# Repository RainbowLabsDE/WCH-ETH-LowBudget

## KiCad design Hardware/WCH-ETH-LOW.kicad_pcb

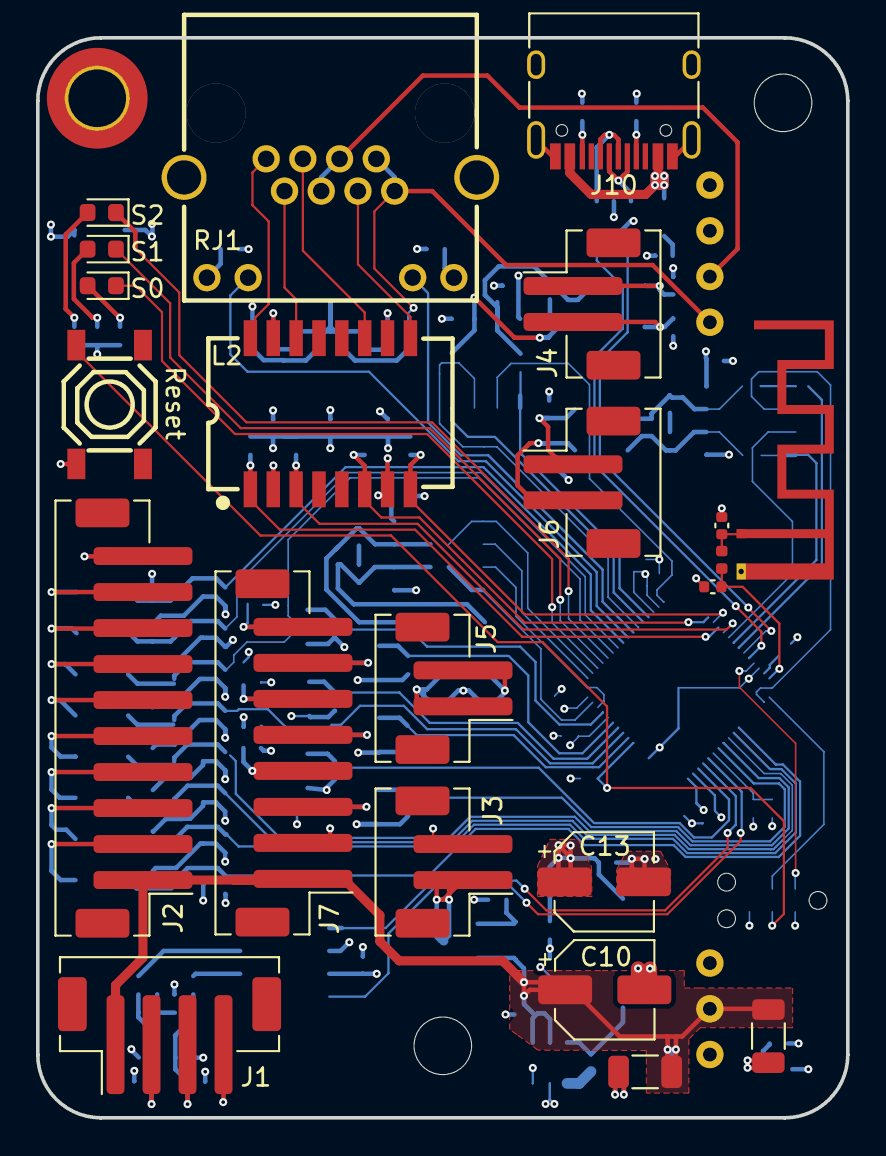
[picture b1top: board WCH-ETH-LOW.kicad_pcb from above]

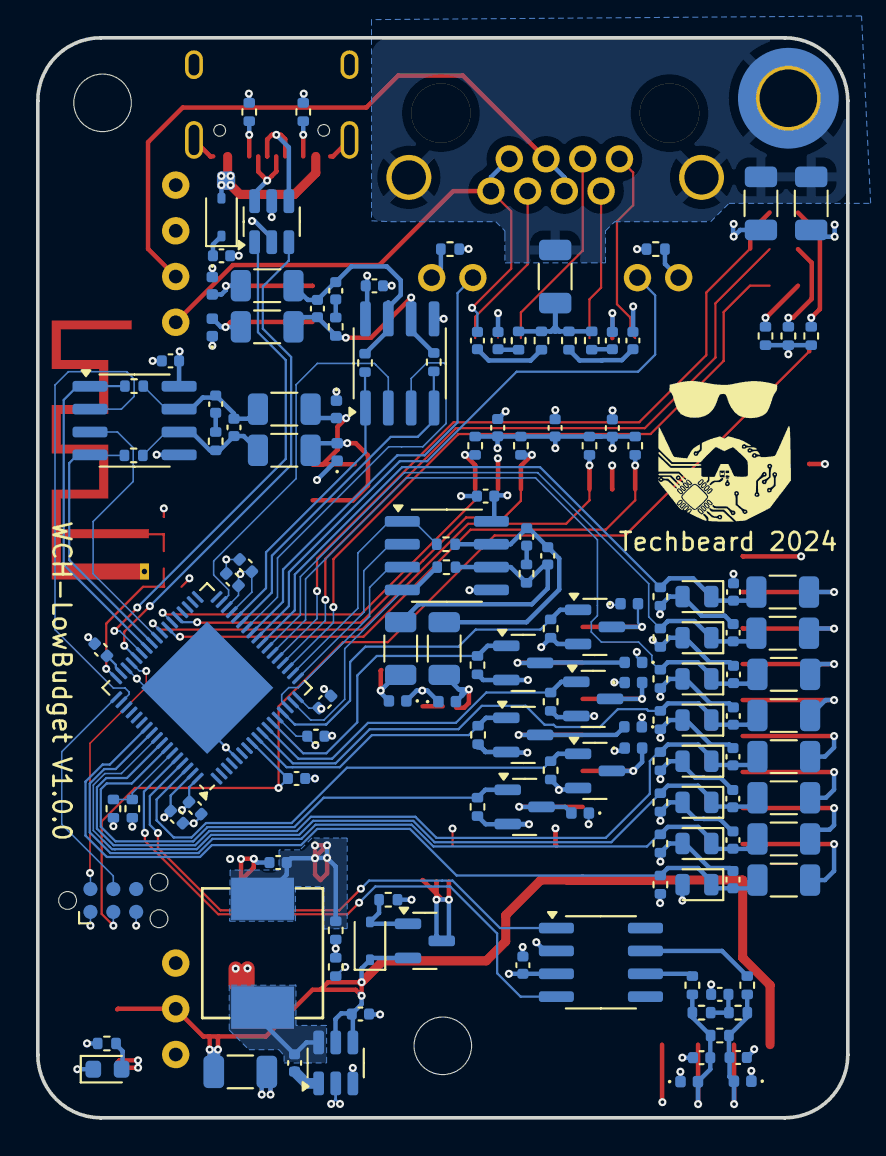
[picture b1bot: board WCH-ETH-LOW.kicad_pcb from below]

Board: 4 copper layers, 45.0 x 60.0 mm, 174 parts (148 on the bottom side), 114 nets.

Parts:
AE1: Antenna_Shield; Texas_SWRA117D_2.4GHz_Left
C1, C2, C4, C7, C8, C9, C11, C12, C15, C16, C19, C21, C22, C23, C24, C25, C26, C27, C28, C29, C30, C31, C33, C34, C36, C37, C38, C39, C40: 100n; C_0402_1005Metric
C3: C; C_0402_1005Metric
C5, C6: 47p; C_0402_1005Metric
C10, C13: 22u; CP_Elec_5x5.4
C14, C43, C44: 10u; C_1206_3216Metric
C17, C18, C20: NC; C_0402_1005Metric
C32, C35: 1000pF/2KV; C_1206_3216Metric
C41, C46: 1u; C_0402_1005Metric
C42, C45: 1p8; C_0402_1005Metric
D1, D2, D7, D8, D9, D10, D11, D12, D20, D21, D22, D23, D24, D25: D_TVS; D_0402_1005Metric
D3, D4, D13, D14, D15, D16, D17, D18: 3V3; D_MicroMELF
D5: 15V; D_SOD-323
D6: PWR; LED_0603_1608Metric
D19: Stat1; LED_0603_1608Metric
D26: Stat2; LED_0603_1608Metric
D27: Stat3; LED_0603_1608Metric
D28: D_Schottky; D_SOD-323
H1: MountingHole_Pad; MountingHole_3.2mm_M3_DIN965_Pad_TopBottom
H2, H3: MountingHole; MountingHole_3.2mm_M3
IC1: RY8310; SOT-23-6
IC2: CH32V208WBU6; QFN-68-1EP_8x8mm_P0.4mm_EP5.2x5.2mm
J1: Conn_01x04_Female; JST_PH_B4B-PH-SM4-TB_1x04-1MP_P2.00mm_Vertical
J2: Conn_01x10_Pin; JST_PH_B10B-PH-SM4-TB_1x10-1MP_P2.00mm_Vertical
J3: Conn_01x02_Pin; JST_PH_B2B-PH-SM4-TB_1x02-1MP_P2.00mm_Vertical
J4, J5, J6: Conn_01x02_Socket; JST_PH_B2B-PH-SM4-TB_1x02-1MP_P2.00mm_Vertical
J7: Conn_01x08_Socket; JST_PH_B8B-PH-SM4-TB_1x08-1MP_P2.00mm_Vertical
J9: Conn_02x03_Odd_Even; Tag-Connect_TC2030-IDC-NL_2x03_P1.27mm_Vertical
J10: USB_C_Receptacle_USB2.0; USB_C_Receptacle_HRO_TYPE-C-31-M-12
L2: B1608S
L3: 4.7u; L_0630
L4: 1n8; L_0402_1005Metric
Q1: AO3401A; SOT-23
Q2, Q4, Q6, Q7, Q8, Q9: AO3400A; SOT-23
R1, R2: 0; R_0402_1005Metric
R3, R5, R6, R15, R16, R17, R27: R; R_0402_1005Metric
R7, R8, R10, R33, R34, R35, R36, R37: 4k7; R_1206_3216Metric
R9: 120; R_0402_1005Metric
R11: 100k; R_0402_1005Metric
R12: 31.25 k; R_0402_1005Metric
R13: 10k; R_0402_1005Metric
R14, R46, R47, R48, R49, R50, R51, R52, R55, R56, R57, R58: 4k7; R_0402_1005Metric
R19, R20, R29: NC; R_0402_1005Metric
R21, R22, R30: 120; C_0402_1005Metric
R23, R24, R25, R26, R31, R32: 10; R_1206_3216Metric
R38, R39, R40, R41, R42, R43, R44, R45: 47k; R_0402_1005Metric
R59: 0; C_1206_3216Metric
R60, R62, R63, R64: 75; R_0402_1005Metric
R61, R65: 1k; R_0402_1005Metric
R66, R67, R68, R69: 49R9; R_0402_1005Metric
R70, R71: 5k1; R_0402_1005Metric
RJ1: R-RJ45R08P-C000; RJ45-TH_R-RJ45R08P-C000
Rê1: R; R_0402_1005Metric
SW1: SW_Push; SW-SMD_4P-L5.1-W5.1-P3.70-LS6.5-TL-2
U1: TCAN330; SOIC-8_3.9x4.9mm_P1.27mm
U2: WE-TVS-82400102; SOT-23-6
U3, U4, U5: MAX3485; SOIC-8_3.9x4.9mm_P1.27mm
U6: RT9400

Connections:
+3.3V: C1.1, C2.1, C4.1, C7.1, C8.1, C12.1, C13.1, C15.1, C16.1, C19.1, C21.1, C22.1, C38.2, C39.2, C40.2, IC2.13 (VDD_A), IC2.17 (Vio_4), IC2.31 (Vio_1), IC2.32 (VDD_1), IC2.67 (Vio_3), IC2.68 (VDD_3), J7.2, J9.1, L2.2 (TCT), L2.7 (RCT), L3.2, R12.2, R14.1, R47.1, R55.1, R56.1, R57.1, R61.1, R65.1, R66.1, R67.1, R68.1, R69.1, U1.3 (VCC), U2.5, U3.8 (VCC), U4.8 (VCC), U5.8 (VCC)
Ant: C45.1, IC2.51 (Ant), L4.2
CAN0_RX: IC2.64 (PB8), U1.4 (RXD)
CAN0_TX: IC2.65 (PB9), U1.1 (TXD)
DIN_00: C24.1, D3.1 (K), IC2.58 (PB3), R7.2, R38.1
DIN_01: C25.1, D4.1 (K), IC2.59 (PB4), R8.2, R39.1
DIN_02: C26.1, D13.1 (K), IC2.60 (PB5), R10.2, R40.1
DIN_03: C27.1, D14.1 (K), IC2.61 (PB6), R33.2, R41.1
DIN_04: C28.1, D15.1 (K), IC2.10 (PC1), R34.2, R42.1
DIN_05: C29.1, D16.1 (K), IC2.23 (PA7), R35.2, R43.1
DIN_06: C30.1, D17.1 (K), IC2.24 (PC4), R36.2, R44.1
DIN_07: C31.1, D18.1 (K), IC2.25 (PC5), R37.2, R45.1
Dout_00: IC2.62 (PB7), Q2.1 (G), R46.2
Dout_01: IC2.66 (PD3), Q4.1 (G), R48.2
Dout_02: IC2.9 (PC0), Q6.1 (G), R49.2
Dout_03: IC2.11 (PC2), Q7.1 (G), R50.2
Dout_04: IC2.12 (PC3), Q8.1 (G), R51.2
Dout_05: IC2.14 (PA0), Q9.1 (G), R52.2
ETH_RXN: IC2.40 (PC7), L2.8 (RD-), R69.2
ETH_RXP: IC2.39 (PC6), L2.6 (RD+), R68.2
ETH_TXN: IC2.42 (PC9), L2.3 (TD-), R67.2
ETH_TXP: IC2.41 (PC8), L2.1 (TD+), R66.2
Earth: C32.1, C35.2, H1.1, R59.1, RJ1.13 (S), RJ1.14 (S)
EthStatLEDL: IC2.27 (PB1), RJ1.10 (L-)
EthStatLEDR: IC2.26 (PB0), RJ1.11 (R+)
GND: AE1.2 (Shield), C1.2, C2.2, C3.1, C4.2, C5.2, C6.2, C7.2, C8.2, C9.2, C10.2, C12.2, C13.2, C14.2, C15.2, C16.2, C19.2, C21.2, C22.2, C23.2, C24.2, C25.2, C26.2, C27.2, C28.2, C29.2, C30.2, C31.2, C32.2, C38.1, C39.1, C40.1, C41.2, C42.2, C43.2, C44.2, C45.2, C46.2, D1.1 (A1), D2.1 (A1), D3.2 (A), D4.2 (A), D6.1 (K), D7.1 (A1), D8.1 (A1), D9.1 (A1), D10.1 (A1), D11.1 (A1), D12.1 (A1), D13.2 (A), D14.2 (A), D15.2 (A), D16.2 (A), D17.2 (A), D18.2 (A), D20.1 (A1), D21.1 (A1), D22.1 (A1), D23.1 (A1), D24.1 (A1), D25.1 (A1), IC1.2 (GND), IC2.5 (Vss_A), IC2.49 (Vss_2), IC2.69 (Vss_Pad), J1.4, J2.10, J3.2, J9.5, J10.A1 (GND), J10.A12 (GND), J10.B1 (GND), J10.B12 (GND), J10.S1 (SHIELD), Q2.2 (S), Q4.2 (S), Q6.2 (S), Q7.2 (S), Q8.2 (S), Q9.2 (S), R11.2, R13.1, R38.2, R39.2, R40.2, R41.2, R42.2, R43.2, R44.2, R45.2, R46.1, R48.1, R49.1, R50.1, R51.1, R52.1, R58.2, R59.2, R70.1, R71.1, SW1.1, U1.2 (GND), U2.2, U3.5 (GND), U4.5 (GND), U5.5 (GND), U6.5 (V-)
NRST: C23.1, IC2.8 (NRST), J9.3, SW1.2
unnamed: AE1.1 (A), C42.1, L4.1
unnamed: C3.2, R5.2, R6.1
unnamed: C17.2, R19.2
unnamed: C18.2, R20.2
unnamed: C20.2, R29.2
unnamed: C33.2, R60.1
unnamed: C34.2, R62.1
unnamed: C35.1, R60.2, R62.2, R63.2, R64.2
unnamed: C36.1, RJ1.4, RJ1.5, U6.3 (B2)
unnamed: C36.2, R63.1
unnamed: C37.1, RJ1.7, RJ1.8, U6.4 (B2)
unnamed: C37.2, R64.1
unnamed: C5.1, D1.2 (A2), J1.2, R1.2, R5.1, R9.1
unnamed: C6.1, D2.2 (A2), J1.3, R2.2, R6.2, R9.2
unnamed: D5.2 (A), Q1.1 (G), R11.1
unnamed: D6.2 (A), R14.2
unnamed: D7.2 (A2), J4.1, R23.2
unnamed: D8.2 (A2), J5.1, R25.2
unnamed: D9.2 (A2), J4.2, R24.2
unnamed: D10.2 (A2), J5.2, R26.2
unnamed: D11.2 (A2), J6.1, R31.2
unnamed: D12.2 (A2), J6.2, R32.2
unnamed: D19.2 (A), R47.2
unnamed: D20.2 (A2), J7.3, Q2.3 (D)
unnamed: D21.2 (A2), J7.4, Q4.3 (D)
unnamed: D22.2 (A2), J7.5, Q6.3 (D)
unnamed: D23.2 (A2), J7.6, Q7.3 (D)
unnamed: D24.2 (A2), J7.7, Q8.3 (D)
unnamed: D25.2 (A2), J7.8, Q9.3 (D)
unnamed: D26.2 (A), R55.2
unnamed: D27.2 (A), R56.2
unnamed: D28.2 (A), J10.A4 (VBUS), J10.A9 (VBUS), J10.B4 (VBUS), J10.B9 (VBUS)
unnamed: C11.1, IC1.1 (CB)
unnamed: IC1.3 (FB), R12.1, R13.2
unnamed: C11.2, IC1.6 (SW), L3.1
unnamed: IC2.63 (BOOT0), R57.2, R58.1
unnamed: J2.2, R7.1
unnamed: J2.3, R8.1
unnamed: J2.4, R10.1
unnamed: J2.5, R33.1
unnamed: J2.6, R34.1
unnamed: J2.7, R35.1
unnamed: J2.8, R36.1
unnamed: J2.9, R37.1
unnamed: J3.1, Q1.3 (D)
unnamed: J10.A5 (CC1), R70.2
unnamed: J10.B5 (CC2), R71.2
unnamed: J10.A6 (D+), J10.B6 (D+), U2.4
unnamed: J10.A7 (D-), J10.B7 (D-), U2.6
unnamed: L2.11 (RX+), RJ1.3
unnamed: L2.9 (RX-), RJ1.6
unnamed: C33.1, L2.10 (RXCT), U6.1 (B1)
unnamed: L2.16 (TX+), RJ1.1
unnamed: L2.14 (TX-), RJ1.2
unnamed: C34.1, L2.15 (TXCT), U6.2 (B1)
unnamed: R61.2, RJ1.9 (L+)
unnamed: R65.2, RJ1.12 (R-)
unnamed: R1.1, U1.7 (CANH)
unnamed: R2.1, U1.6 (CANL)
RS485_00_A: R16.2, R19.1, R21.2, R24.1, U3.6 (A)
RS485_00_B: C17.1, R15.2, R21.1, R23.1, U3.7 (B)
RS485_00_DE: IC2.28 (PB2), U3.3 (DE)
RS485_00_DI: IC2.29 (PB10), R16.1, U3.4 (DI)
RS485_00_RE: IC2.33 (PD5), U3.2 (~RE)
RS485_00_RO: IC2.30 (PB11), R15.1, U3.1 (RO)
RS485_01_A: R3.2, R29.1, R30.2, R32.1, U5.6 (A)
RS485_01_B: C20.1, R27.2, R30.1, R31.1, U5.7 (B)
RS485_01_DE: IC2.43 (PA8), U5.3 (DE)
RS485_01_DI: IC2.44 (PA9), R3.1, U5.4 (DI)
RS485_01_RE: IC2.53 (PA15), U5.2 (~RE)
RS485_01_RO: IC2.45 (PA10), R27.1, U5.1 (RO)
RS485_02_A: R20.1, R22.2, R26.1, Rê1.2, U4.6 (A)
RS485_02_B: C18.1, R17.2, R22.1, R25.1, U4.7 (B)
RS485_02_DE: IC2.15 (PA1), U4.3 (DE)
RS485_02_DI: IC2.16 (PA2), Rê1.1, U4.4 (DI)
RS485_02_RE: IC2.18 (PD4), U4.2 (~RE)
RS485_02_RO: IC2.19 (PA3), R17.1, U4.1 (RO)
SWCLK: IC2.52 (PA14), J9.4
SWD: IC2.48 (PA13), J9.2
StatLED00: D19.1 (K), IC2.20 (PA4)
StatLED01: D26.1 (K), IC2.21 (PA5)
StatLED02: D27.1 (K), IC2.22 (PA6)
USB1DN: IC2.46 (PA11), U2.1
USB1DP: IC2.47 (PA12), U2.3
VBUS: C41.1, D28.1 (K)
VCC: C9.1, C10.1, C14.1, C43.1, C44.1, D5.1 (K), IC1.4 (EN), IC1.5 (IN), J1.1, J2.1, J7.1, Q1.2 (S), U6.6 (V+)
Vinta: C46.1, IC2.50 (Vinta)

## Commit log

2024-03-29 initial
2024-04-24 Working MQTT Example
2024-04-24 beispiel code funktioniert
2024-04-26 to firmware folder
2024-04-27 add Hardware zu git
